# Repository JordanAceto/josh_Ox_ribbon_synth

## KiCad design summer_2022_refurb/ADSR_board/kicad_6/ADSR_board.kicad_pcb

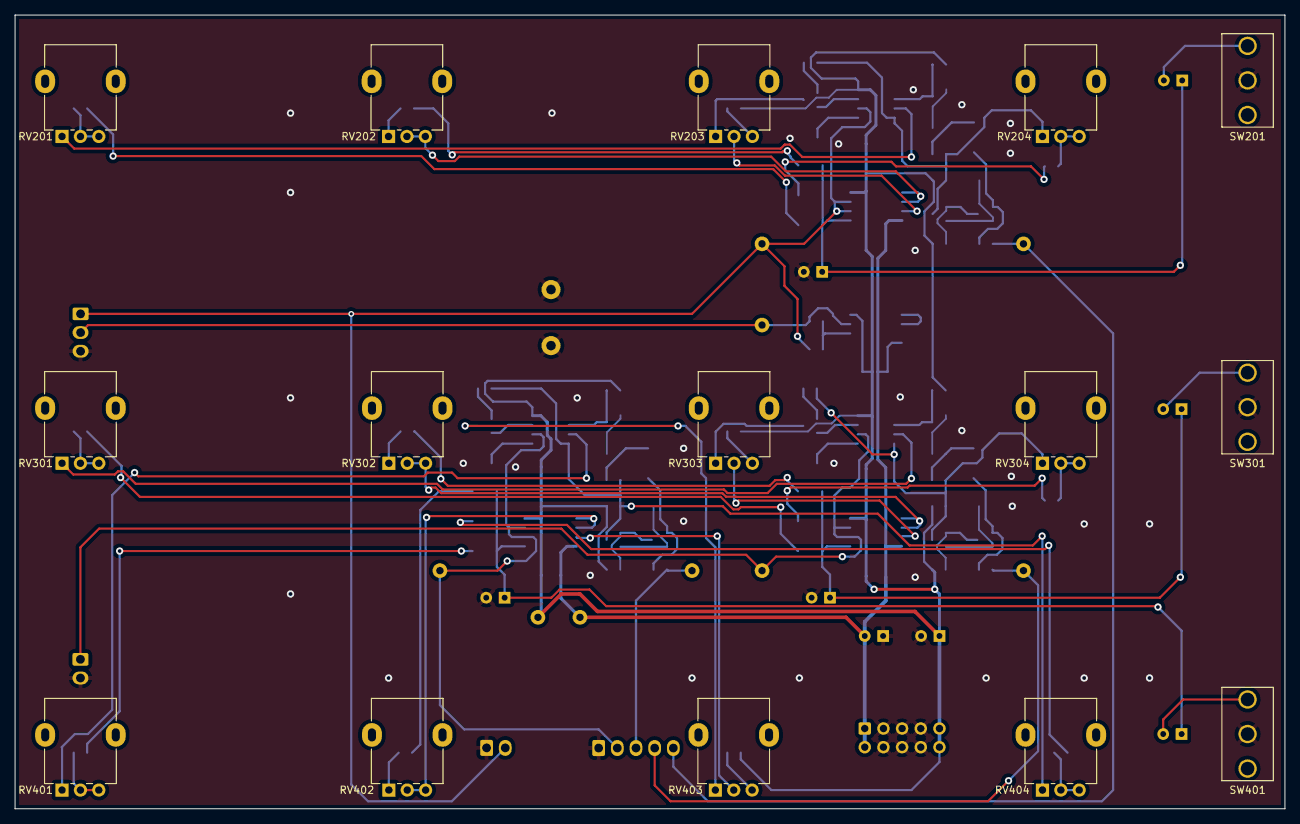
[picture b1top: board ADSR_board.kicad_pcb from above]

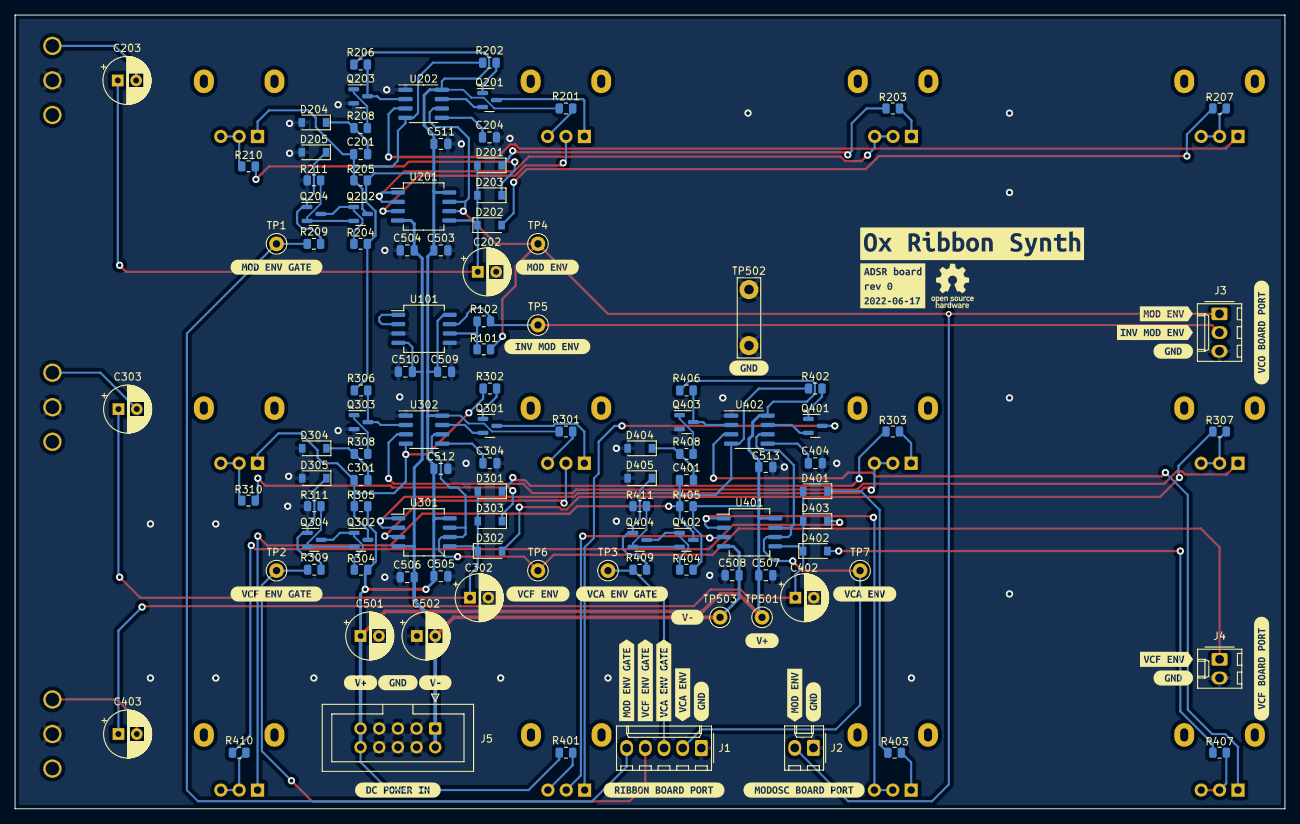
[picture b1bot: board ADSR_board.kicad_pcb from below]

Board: 2 copper layers, 172.7 x 107.9 mm, 156 parts (141 on the bottom side), 81 nets.

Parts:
C201, C204, C301, C304, C401, C404: 10n; C_0805_2012Metric
C202, C302, C402: 2u2; CP_Radial_D6.3mm_P2.50mm
C203, C303, C403: 22u; CP_Radial_D6.3mm_P2.50mm
C501, C502: 10u; CP_Radial_D6.3mm_P2.50mm
C503, C504, C505, C506, C507, C508, C509, C510, C511, C512, C513: 100n; C_0805_2012Metric
D201, D202, D203, D204, D205, D301, D302, D303, D304, D305, D401, D402, D403, D404, D405: 1N4148W; D_SOD-123
J1: ribbon_port; Molex_KK-254_AE-6410-05A_1x05_P2.54mm_Vertical
J2: modosc_port; Molex_KK-254_AE-6410-02A_1x02_P2.54mm_Vertical
J3: VCO_port; Molex_KK-254_AE-6410-03A_1x03_P2.54mm_Vertical
J4: VCF_port; Molex_KK-254_AE-6410-02A_1x02_P2.54mm_Vertical
J5: power_entry; IDC-Header_2x05_P2.54mm_Vertical
Q201, Q301, Q401: 2N7002; SOT-23
Q202, Q203, Q204, Q302, Q303, Q304, Q402, Q403, Q404: MMBT3904; SOT-23
R101, R102, R209, R309, R409: 100k; R_0805_2012Metric
R201, R301, R401: 4k7; R_0805_2012Metric
R202, R302, R402: 1M; R_0805_2012Metric
R203, R210, R211, R303, R310, R311, R403, R410, R411: 100; R_0805_2012Metric
R204, R205, R206, R208, R304, R305, R306, R308, R404, R405, R406, R408: 10k; R_0805_2012Metric
R207, R307, R407: 680; R_0805_2012Metric
RV201, RV202, RV204, RV301, RV302, RV304, RV401, RV402, RV404: 500kA; Potentiometer_Alpha_RD901F-40-00D_Single_Vertical
RV203, RV303, RV403: 10k; Potentiometer_Alpha_RD901F-40-00D_Single_Vertical
SW201, SW301, SW401: SW_SPDT; SPDT_mini_toggle
TP1: mod env gate; TestPoint_Keystone_5000-5004_Miniature
TP2: VCF env gate; TestPoint_Keystone_5000-5004_Miniature
TP3: VCA env gate; TestPoint_Keystone_5000-5004_Miniature
TP4: mod env; TestPoint_Keystone_5000-5004_Miniature
TP5: inv mod env; TestPoint_Keystone_5000-5004_Miniature
TP6: VCF env; TestPoint_Keystone_5000-5004_Miniature
TP7: VCA env; TestPoint_Keystone_5000-5004_Miniature
TP501: V+; TestPoint_Keystone_5000-5004_Miniature
TP502: GND; TestPoint_Bridge_Pitch7.62mm_Drill1.3mm
TP503: V-; TestPoint_Keystone_5000-5004_Miniature
U101, U201, U301, U401: TL072; SO-8_5.3x6.2mm_P1.27mm
U202, U302, U402: LM555xM; SOIC-8_3.9x4.9mm_P1.27mm
kibuzzard-62AC7A9F: G***; kibuzzard-62AC7A9F
kibuzzard-62AC7ABD: G***; kibuzzard-62AC7ABD
kibuzzard-62AC77C9: G***; kibuzzard-62AC77C9
kibuzzard-62AC77E4: G***; kibuzzard-62AC77E4
kibuzzard-62AC77FB: G***; kibuzzard-62AC77FB
kibuzzard-62AC78CB: G***; kibuzzard-62AC78CB
kibuzzard-62AC79A3: G***; kibuzzard-62AC79A3
kibuzzard-62AC79B4: G***; kibuzzard-62AC79B4
kibuzzard-62AC79C5: G***; kibuzzard-62AC79C5
kibuzzard-62AC79E0: G***; kibuzzard-62AC79E0
kibuzzard-62AC755C, kibuzzard-62AC755C#2, kibuzzard-62AC755C#3, kibuzzard-62AC755C#4, kibuzzard-62AC755C#5, kibuzzard-62AC755C#6: G***; kibuzzard-62AC755C
kibuzzard-62AC758B: G***; kibuzzard-62AC758B
kibuzzard-62AC762D: G***; kibuzzard-62AC762D
kibuzzard-62AC769B: G***; kibuzzard-62AC769B
kibuzzard-62AC791A, kibuzzard-62AC791A#2: G***; kibuzzard-62AC791A
kibuzzard-62AC792A, kibuzzard-62AC792A#2: G***; kibuzzard-62AC792A
kibuzzard-62AC795F: G***; kibuzzard-62AC795F
kibuzzard-62AC7596: G***; kibuzzard-62AC7596
kibuzzard-62AC7711: G***; kibuzzard-62AC7711
kibuzzard-62AC7737: G***; kibuzzard-62AC7737
kibuzzard-62AC7758: G***; kibuzzard-62AC7758
kibuzzard-62AC7771: G***; kibuzzard-62AC7771
kibuzzard-62AC7810: G***; kibuzzard-62AC7810
kibuzzard-62AC7972: G***; kibuzzard-62AC7972
kibuzzard-62AC7989: G***; kibuzzard-62AC7989

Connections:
+15V: C501.1, C503.1, C505.1, C507.1, C509.1, C511.1, C512.1, C513.1, J5.9, J5.10, R201.1, R204.1, R205.1, R206.1, R301.1, R304.1, R305.1, R306.1, R401.1, R404.1, R405.1, R406.1, TP501.1, U101.8 (V+), U201.8 (V+), U202.8 (VCC), U301.8 (V+), U302.8 (VCC), U401.8 (V+), U402.8 (VCC)
-15V: C502.2, C504.2, C506.2, C508.2, C510.2, J5.1, J5.2, TP503.1, U101.4 (V-), U201.4 (V-), U301.4 (V-), U401.4 (V-)
/VCA_ADSR/GATE: J1.3, R409.1, TP3.1
/VCA_ENV: J1.2, TP7.1, U401.6 (-), U401.7, U402.6 (THR)
/VCF_ADSR/GATE: J1.4, R309.1, TP2.1
/VCF_ADSR/OUT: J4.1, TP6.1, U301.6 (-), U301.7, U302.6 (THR)
/modulation_ADSR/GATE: J1.5, R209.1, TP1.1
/modulation_ADSR/OUT: J2.2, J3.1, R101.1, TP4.1, U201.6 (-), U201.7, U202.6 (THR)
GND: C202.2, C204.2, C302.2, C304.2, C402.2, C404.2, C501.2, C502.1, C503.2, C504.1, C505.2, C506.1, C507.2, C508.1, C509.2, C510.1, C511.2, C512.2, C513.2, D204.2 (A), D205.2 (A), D304.2 (A), D305.2 (A), D404.2 (A), D405.2 (A), J1.1, J2.1, J3.3, J4.2, J5.3, J5.4, J5.5, J5.6, J5.7, J5.8, Q203.2 (E), Q303.2 (E), Q403.2 (E), R211.2, R311.2, R411.2, SW201.2 (B), SW301.2 (B), SW401.2 (B), TP502.1, U101.3 (+), U101.5 (+), U202.1 (GND), U302.1 (GND), U402.1 (GND)
unnamed: C201.1, Q202.3 (C), R202.1, R205.2, RV204.1, U202.4 (R)
unnamed: C201.2, D204.1 (K), R208.1
unnamed: C202.1, C203.1, D201.2 (A), D202.1 (K), D203.2 (A), U201.5 (+)
unnamed: C203.2, SW201.3 (C)
unnamed: C204.1, U202.5 (CV)
unnamed: C301.1, Q302.3 (C), R302.1, R305.2, RV304.1, U302.4 (R)
unnamed: C301.2, D304.1 (K), R308.1
unnamed: C302.1, C303.1, D301.2 (A), D302.1 (K), D303.2 (A), U301.5 (+)
unnamed: C303.2, SW301.3 (C)
unnamed: C304.1, U302.5 (CV)
unnamed: C401.1, Q402.3 (C), R402.1, R405.2, RV404.1, U402.4 (R)
unnamed: C401.2, D404.1 (K), R408.1
unnamed: C402.1, C403.1, D401.2 (A), D402.1 (K), D403.2 (A), U401.5 (+)
unnamed: C403.2, SW401.3 (C)
unnamed: C404.1, U402.5 (CV)
unnamed: D201.1 (K), R203.2
unnamed: D202.2 (A), R207.2
unnamed: D203.1 (K), R210.1
unnamed: D205.1 (K), Q204.1 (B), R209.2
unnamed: D301.1 (K), R303.2
unnamed: D302.2 (A), R307.2
unnamed: D303.1 (K), R310.1
unnamed: D305.1 (K), Q304.1 (B), R309.2
unnamed: D401.1 (K), R403.2
unnamed: D402.2 (A), R407.2
unnamed: D403.1 (K), R410.1
unnamed: D405.1 (K), Q404.1 (B), R409.2
unnamed: J3.2, R102.2, TP5.1, U101.7
unnamed: Q201.1 (G), R202.2
unnamed: Q201.2 (S), U202.7 (DIS)
unnamed: Q201.3 (D), RV203.1
unnamed: Q202.1 (B), Q204.3 (C), R204.2
unnamed: Q202.2 (E), Q204.2 (E), R211.1
unnamed: Q203.1 (B), R208.2
unnamed: Q203.3 (C), R206.2, U202.2 (TR)
unnamed: Q301.1 (G), R302.2
unnamed: Q301.2 (S), U302.7 (DIS)
unnamed: Q301.3 (D), RV303.1
unnamed: Q302.1 (B), Q304.3 (C), R304.2
unnamed: Q302.2 (E), Q304.2 (E), R311.1
unnamed: Q303.1 (B), R308.2
unnamed: Q303.3 (C), R306.2, U302.2 (TR)
unnamed: Q401.1 (G), R402.2
unnamed: Q401.2 (S), U402.7 (DIS)
unnamed: Q401.3 (D), RV403.1
unnamed: Q402.1 (B), Q404.3 (C), R404.2
unnamed: Q402.2 (E), Q404.2 (E), R411.1
unnamed: Q403.1 (B), R408.2
unnamed: Q403.3 (C), R406.2, U402.2 (TR)
unnamed: R101.2, R102.1, U101.6 (-)
unnamed: R201.2, RV203.3
unnamed: R203.1, RV202.1
unnamed: R207.1, RV201.2, RV201.3
unnamed: R210.2, RV204.2, RV204.3
unnamed: R301.2, RV303.3
unnamed: R303.1, RV302.1
unnamed: R307.1, RV301.2, RV301.3
unnamed: R310.2, RV304.2, RV304.3
unnamed: R401.2, RV403.3
unnamed: R403.1, RV402.1
unnamed: R407.1, RV401.2, RV401.3
unnamed: R410.2, RV404.2, RV404.3
unnamed: RV201.1, U202.3 (Q)
unnamed: RV202.2, RV202.3, U201.1, U201.2 (-)
unnamed: RV203.2, U201.3 (+)
unnamed: RV301.1, U302.3 (Q)
unnamed: RV302.2, RV302.3, U301.1, U301.2 (-)
unnamed: RV303.2, U301.3 (+)
unnamed: RV401.1, U402.3 (Q)
unnamed: RV402.2, RV402.3, U401.1, U401.2 (-)
unnamed: RV403.2, U401.3 (+)
unnamed: U101.1, U101.2 (-)

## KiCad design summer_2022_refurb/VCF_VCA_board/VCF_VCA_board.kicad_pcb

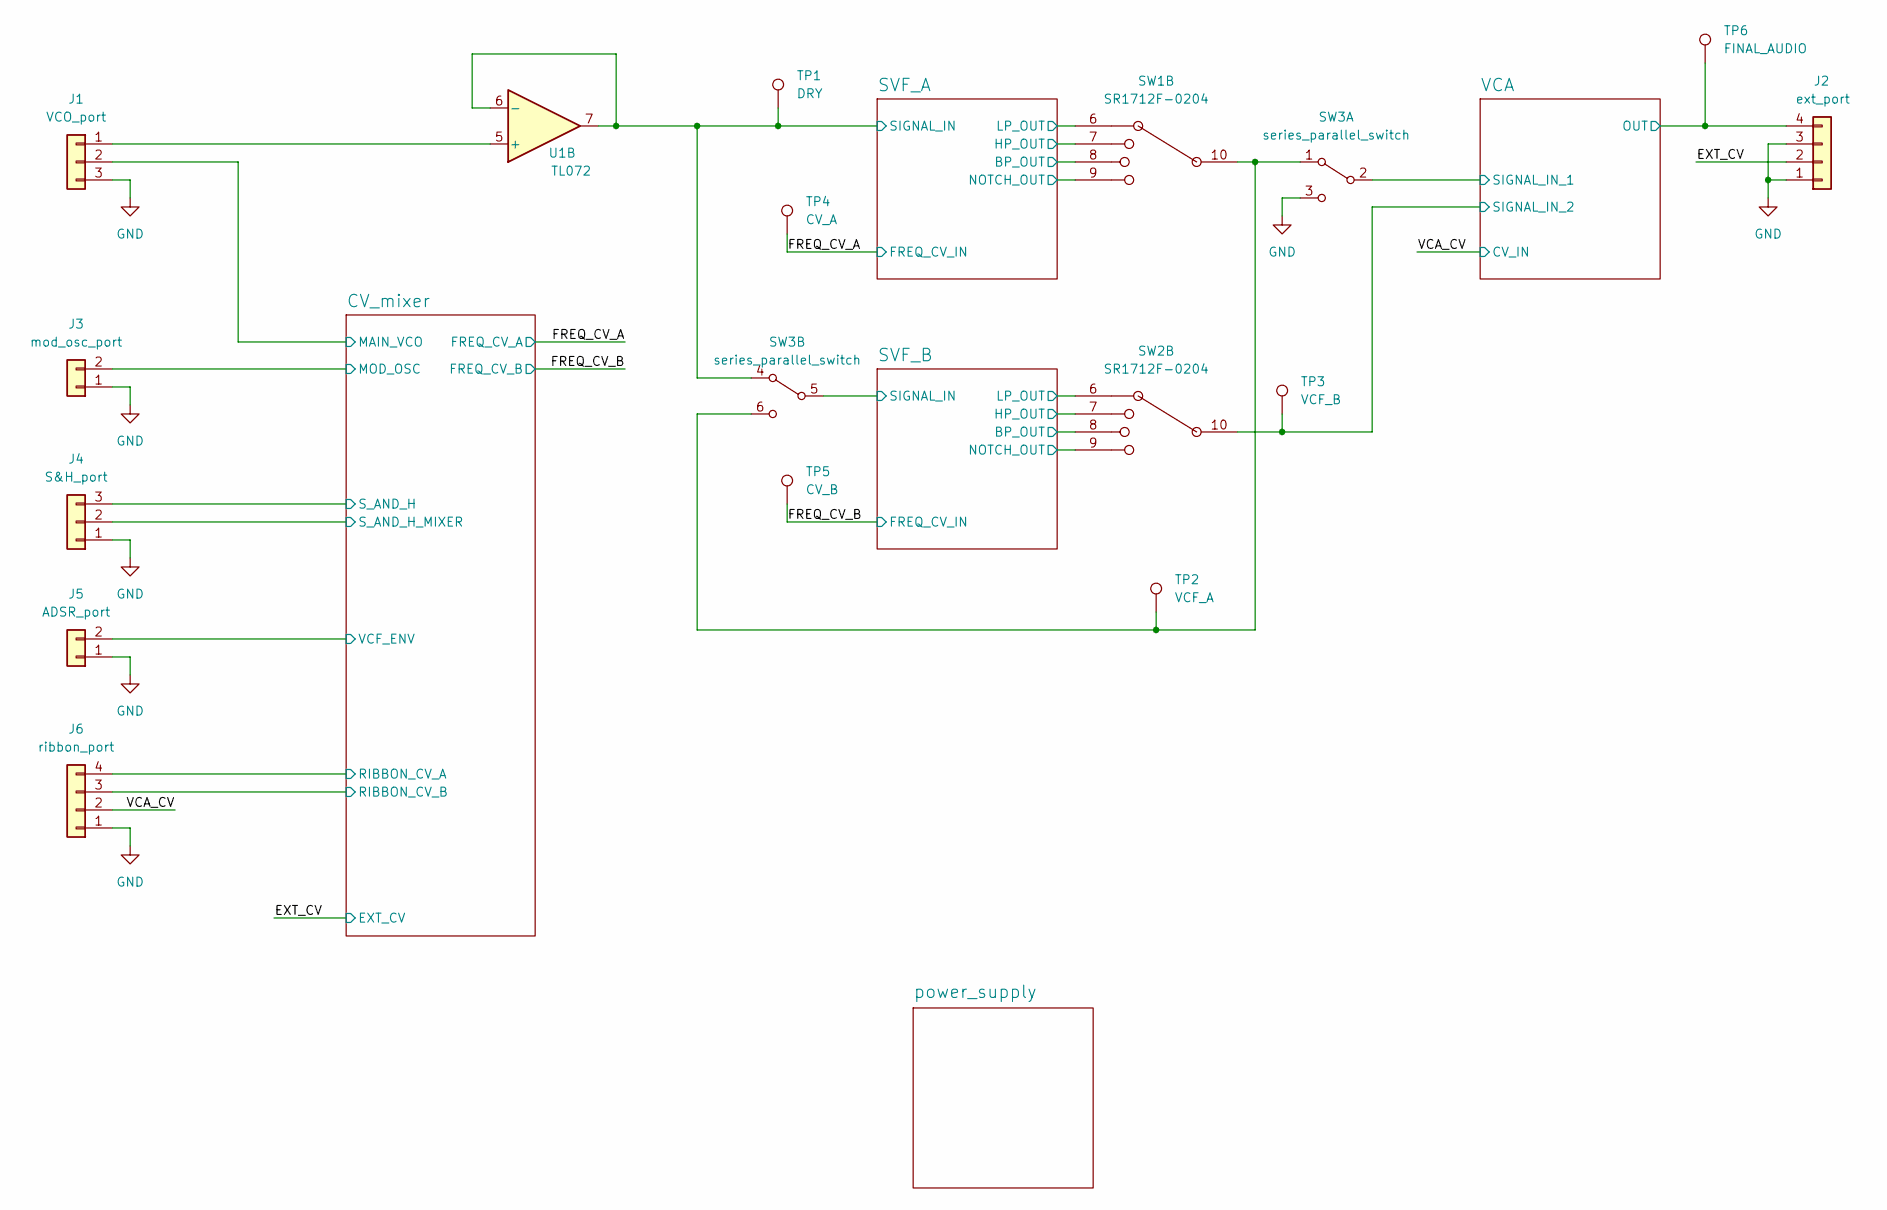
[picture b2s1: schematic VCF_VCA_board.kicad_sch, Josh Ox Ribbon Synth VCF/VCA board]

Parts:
J1: VCO_port; Molex_KK-254_AE-6410-03A_1x03_P2.54mm_Vertical
J2: ext_port; Molex_KK-254_AE-6410-04A_1x04_P2.54mm_Vertical
J3: mod_osc_port; Molex_KK-254_AE-6410-02A_1x02_P2.54mm_Vertical
J4: S&H_port; Molex_KK-254_AE-6410-03A_1x03_P2.54mm_Vertical
J5: ADSR_port; Molex_KK-254_AE-6410-02A_1x02_P2.54mm_Vertical
J6: ribbon_port; Molex_KK-254_AE-6410-04A_1x04_P2.54mm_Vertical
SW1, SW2: SR1712F-0204; SR1712F_rotary_switch
SW3: series_parallel_switch; DPDT_mini_toggle
TP1: DRY; TestPoint_Keystone_5000-5004_Miniature
TP2: VCF_A; TestPoint_Keystone_5000-5004_Miniature
TP3: VCF_B; TestPoint_Keystone_5000-5004_Miniature
TP4: CV_A; TestPoint_Keystone_5000-5004_Miniature
TP5: CV_B; TestPoint_Keystone_5000-5004_Miniature
TP6: FINAL_AUDIO; TestPoint_Keystone_5000-5004_Miniature
U1: TL072; SO-8_5.3x6.2mm_P1.27mm

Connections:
/CV_mixer/MAIN_VCO: J1.2; also elsewhere on the board
/CV_mixer/MOD_OSC: J3.2; also elsewhere on the board
/CV_mixer/RIBBON_CV_A: J6.4; also elsewhere on the board
/CV_mixer/RIBBON_CV_B: J6.3; also elsewhere on the board
/CV_mixer/S_AND_H: J4.3; also elsewhere on the board
/CV_mixer/S_AND_H_MIXER: J4.2; also elsewhere on the board
/CV_mixer/VCF_ENV: J5.2; also elsewhere on the board
/EXT_CV: J2.2; also elsewhere on the board
/FREQ_CV_A: TP4.1; also elsewhere on the board
/FREQ_CV_B: TP5.1; also elsewhere on the board
/SVF_A/BP_OUT: SW1.8; also elsewhere on the board
/SVF_A/HP_OUT: SW1.7; also elsewhere on the board
/SVF_A/LP_OUT: SW1.6; also elsewhere on the board
/SVF_A/NOTCH_OUT: SW1.9; also elsewhere on the board
/SVF_A/SIGNAL_IN: SW3.4 (A), TP1.1, U1.6 (-), U1.7; also elsewhere on the board
/SVF_B/BP_OUT: SW2.8; also elsewhere on the board
/SVF_B/HP_OUT: SW2.7; also elsewhere on the board
/SVF_B/LP_OUT: SW2.6; also elsewhere on the board
/SVF_B/NOTCH_OUT: SW2.9; also elsewhere on the board
/SVF_B/SIGNAL_IN: SW3.5 (B); also elsewhere on the board
/VCA/OUT: J2.4, TP6.1; also elsewhere on the board
/VCA/SIGNAL_IN_1: SW3.2 (B); also elsewhere on the board
/VCA/SIGNAL_IN_2: SW2.10, TP3.1; also elsewhere on the board
/VCA_CV: J6.2; also elsewhere on the board
unnamed: J1.1, U1.5 (+)
unnamed: SW1.10, SW3.1 (A), SW3.6 (C), TP2.1

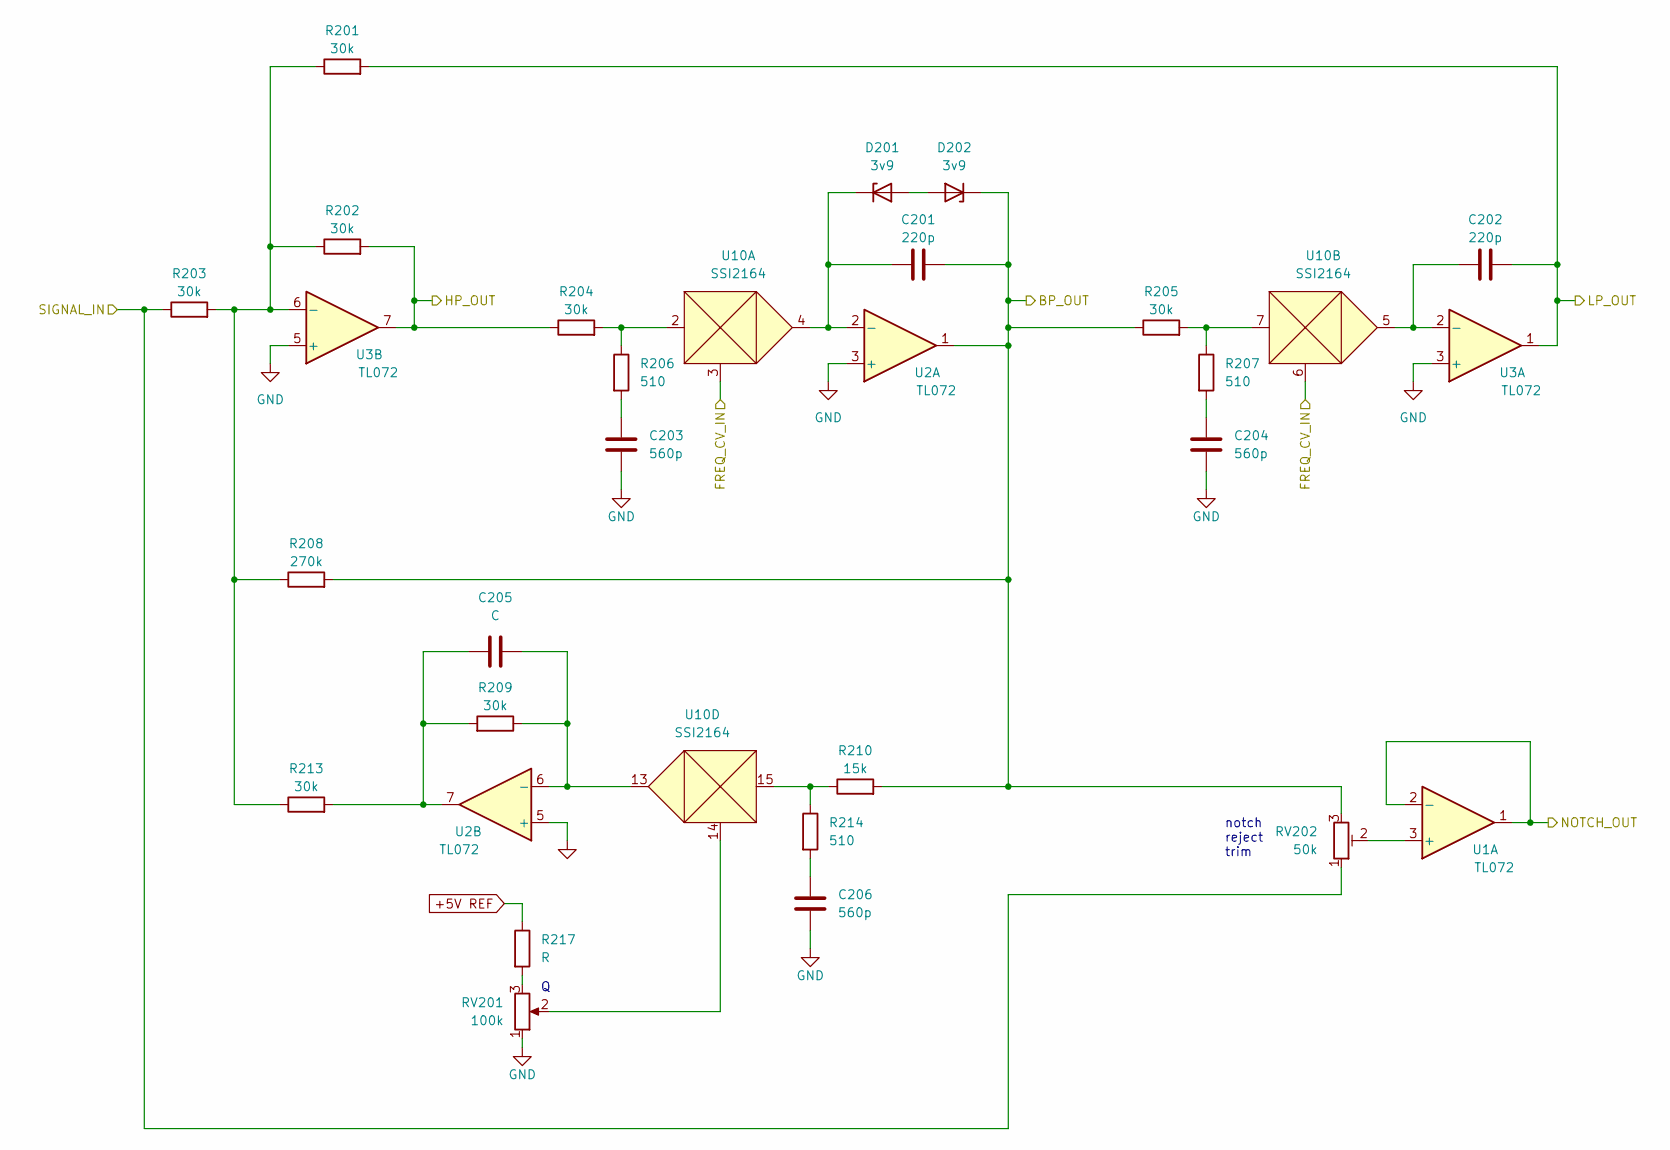
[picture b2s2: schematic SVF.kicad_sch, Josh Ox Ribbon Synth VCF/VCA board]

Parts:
C201, C202: 220p; C_Rect_L7.2mm_W4.5mm_P5.00mm_FKS2_FKP2_MKS2_MKP2
C203, C204, C206: 560p; C_0805_2012Metric
C205: C; C_0805_2012Metric
D201, D202: 3v9; D_SOD-123
R201, R202, R203, R204, R205, R209, R213: 30k; R_0805_2012Metric
R206, R207, R214: 510; R_0805_2012Metric
R208: 270k; R_0805_2012Metric
R210: 15k; R_0805_2012Metric
R217: R; R_0805_2012Metric
RV201: 100k; Potentiometer_Alpha_RD901F-40-00D_Single_Vertical
RV202: 50k; Potentiometer_Bourns_3296W_Vertical
U1, U2, U3: TL072; SO-8_5.3x6.2mm_P1.27mm
U10: SSI2164; SOIC-16_3.9x9.9mm_P1.27mm

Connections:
+5V REF: R217.1; also elsewhere on the board
/FREQ_CV_A: U10.3, U10.6; also elsewhere on the board
/SVF_A/BP_OUT: C201.2, D202.1 (K), R205.1, R208.2, R210.2, RV202.3, U2.1; also elsewhere on the board
/SVF_A/HP_OUT: R202.2, R204.1, U3.7; also elsewhere on the board
/SVF_A/LP_OUT: C202.2, R201.2, U3.1; also elsewhere on the board
/SVF_A/NOTCH_OUT: U1.1, U1.2 (-); also elsewhere on the board
/SVF_A/SIGNAL_IN: R203.1, RV202.1; also elsewhere on the board
unnamed: C201.1, D201.1 (K), U2.2 (-), U10.4
unnamed: C202.1, U3.2 (-), U10.5
unnamed: C203.1, R206.2
unnamed: C204.1, R207.2
unnamed: C205.1, R209.2, R213.2, U2.7
unnamed: C205.2, R209.1, U2.6 (-), U10.13
unnamed: C206.1, R214.2
unnamed: D201.2 (A), D202.2 (A)
unnamed: R201.1, R202.1, R203.2, R208.1, R213.1, U3.6 (-)
unnamed: R204.2, R206.1, U10.2
unnamed: R205.2, R207.1, U10.7
unnamed: R210.1, R214.1, U10.15
unnamed: R217.2, RV201.3
unnamed: RV201.2, U10.14
unnamed: RV202.2, U1.3 (+)

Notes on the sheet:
notch reject trim

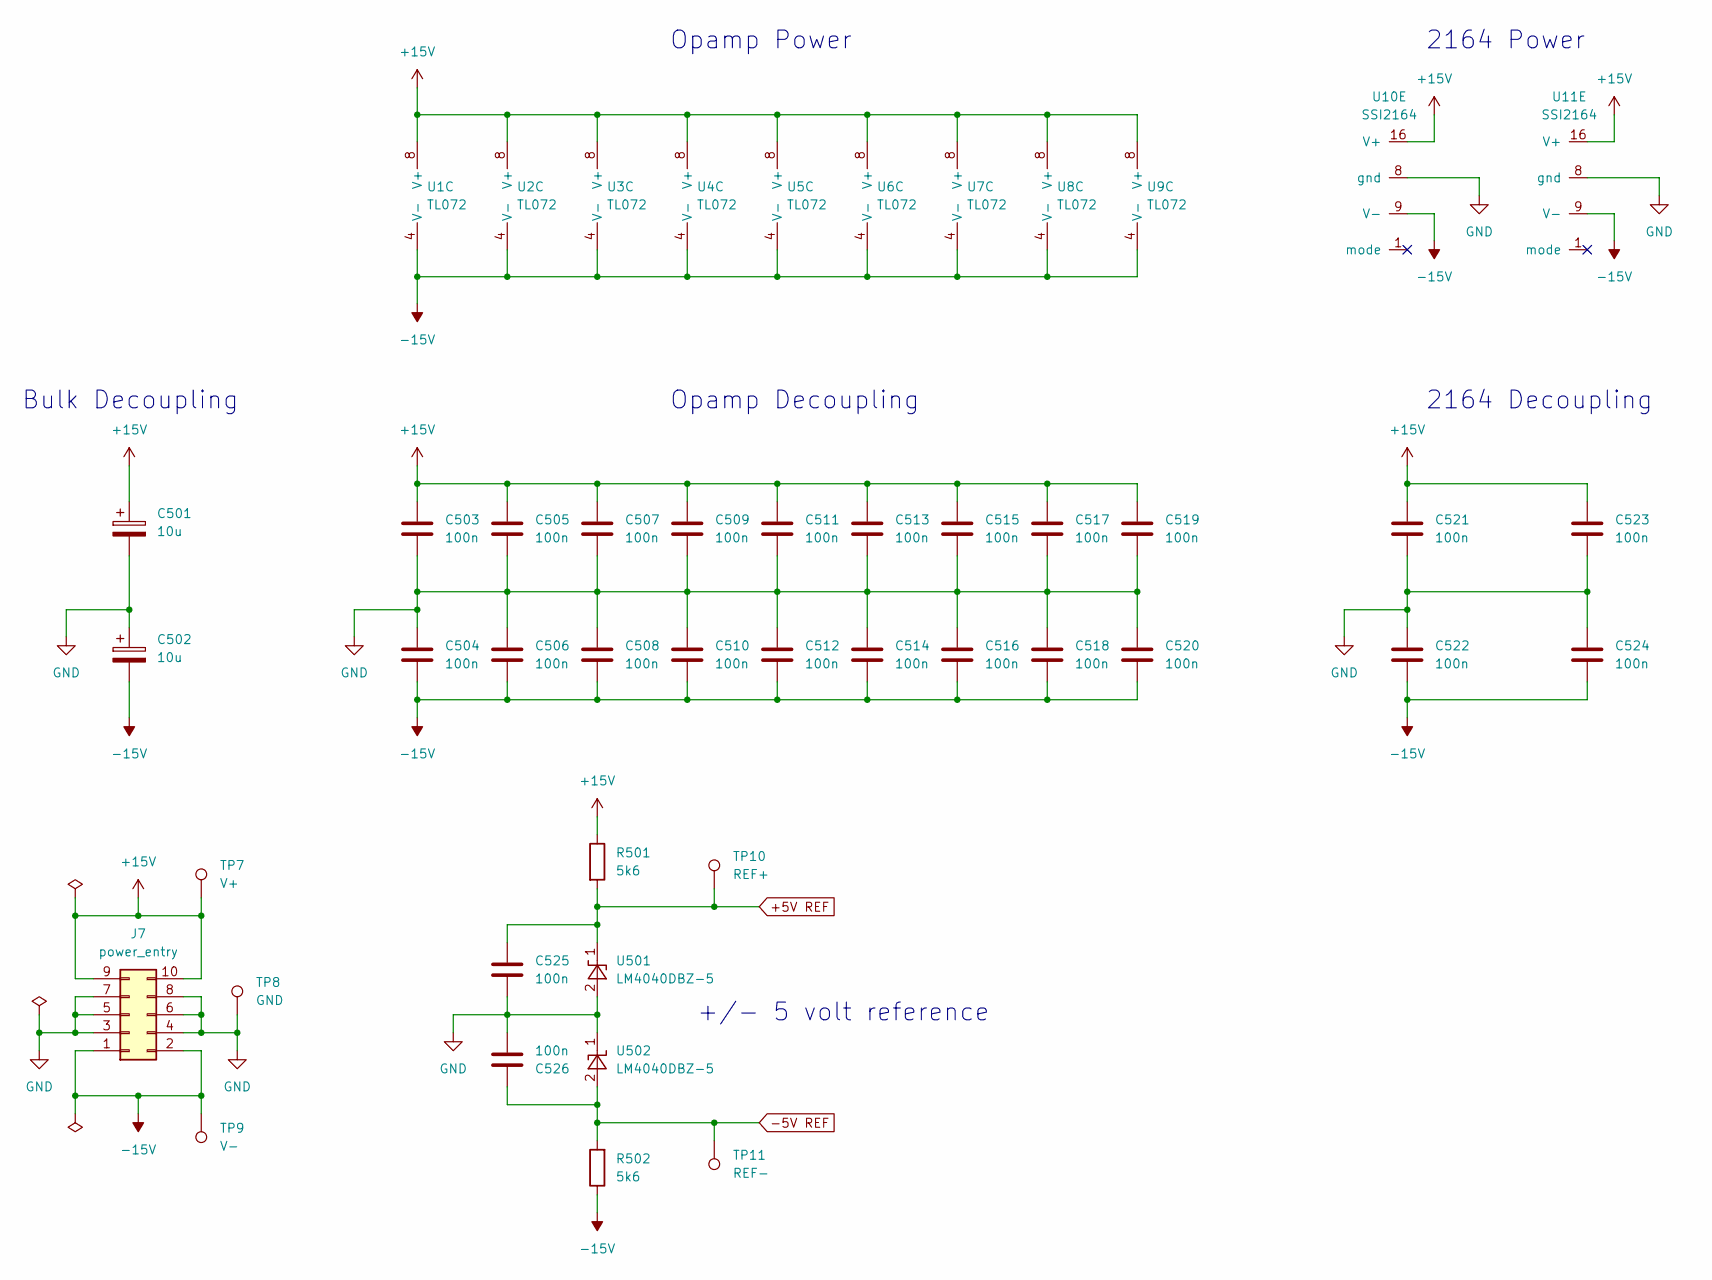
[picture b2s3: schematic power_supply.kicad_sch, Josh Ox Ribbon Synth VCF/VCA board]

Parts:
C501, C502: 10u; CP_Radial_D6.3mm_P2.50mm
C503, C504, C505, C506, C507, C508, C509, C510, C511, C512, C513, C514, C515, C516, C517, C518, C519, C520, C521, C522, C523, C524, C525, C526: 100n; C_0805_2012Metric
J7: power_entry; IDC-Header_2x05_P2.54mm_Vertical
R501, R502: 5k6; R_0805_2012Metric
TP7: V+; TestPoint_Keystone_5000-5004_Miniature
TP8: GND; TestPoint_Bridge_Pitch7.62mm_Drill1.3mm
TP9: V-; TestPoint_Keystone_5000-5004_Miniature
TP10: REF+; TestPoint_Keystone_5000-5004_Miniature
TP11: REF-; TestPoint_Keystone_5000-5004_Miniature
U1, U2, U3, U4, U5, U6, U7, U8, U9: TL072; SO-8_5.3x6.2mm_P1.27mm
U10, U11: SSI2164; SOIC-16_3.9x9.9mm_P1.27mm
U501, U502: LM4040DBZ-5; SOT-23

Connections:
+5V REF: C525.1, R501.2, TP10.1, U501.1 (K); also elsewhere on the board
+15V: C501.1, C503.1, C505.1, C507.1, C509.1, C511.1, C513.1, C515.1, C517.1, C519.1, C521.1, C523.1, J7.9, J7.10, R501.1, TP7.1, U1.8 (V+), U2.8 (V+), U3.8 (V+), U4.8 (V+), U5.8 (V+), U6.8 (V+), U7.8 (V+), U8.8 (V+), U9.8 (V+), U10.16 (V+), U11.16 (V+)
-5V REF: C526.1, R502.2, TP11.1, U502.2 (A); also elsewhere on the board
-15V: C502.2, C504.2, C506.2, C508.2, C510.2, C512.2, C514.2, C516.2, C518.2, C520.2, C522.2, C524.2, J7.1, J7.2, R502.1, TP9.1, U1.4 (V-), U2.4 (V-), U3.4 (V-), U4.4 (V-), U5.4 (V-), U6.4 (V-), U7.4 (V-), U8.4 (V-), U9.4 (V-), U10.9 (V-), U11.9 (V-)
/FREQ_CV_B: U11.3, U11.6; also elsewhere on the board
/SVF_B/BP_OUT: U4.1; also elsewhere on the board
/SVF_B/HP_OUT: U5.7; also elsewhere on the board
/SVF_B/LP_OUT: U5.1; also elsewhere on the board
/SVF_B/NOTCH_OUT: U6.6 (-), U6.7; also elsewhere on the board
unnamed 35: U4.2 (-), U11.4; also elsewhere on the board
unnamed 36: U5.2 (-), U11.5; also elsewhere on the board
unnamed 39: U4.7; also elsewhere on the board
unnamed 40: U4.6 (-), U11.13; also elsewhere on the board
unnamed 68: U5.6 (-); also elsewhere on the board
unnamed 69: U11.2; also elsewhere on the board
unnamed 70: U11.7; also elsewhere on the board
unnamed 71: U11.15; also elsewhere on the board
unnamed 90: U11.14; also elsewhere on the board
unnamed 91: U6.5 (+); also elsewhere on the board

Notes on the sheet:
Opamp Power
2164 Decoupling
+/- 5 volt reference
2164 Power
Bulk Decoupling
Opamp Decoupling

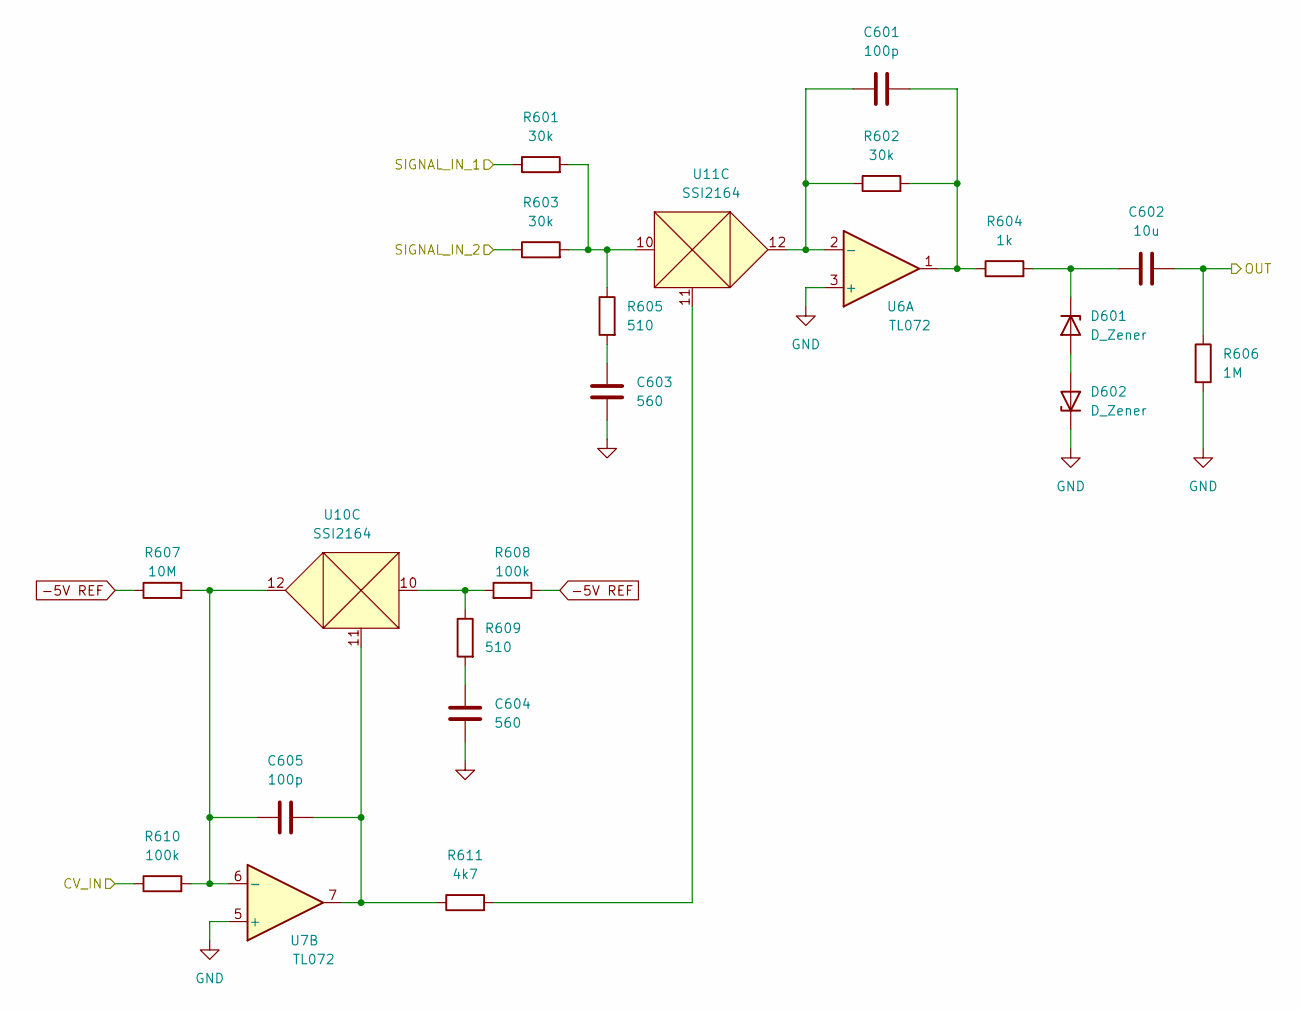
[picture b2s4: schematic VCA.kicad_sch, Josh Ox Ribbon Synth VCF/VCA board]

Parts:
C601, C605: 100p; C_0805_2012Metric
C602: 10u; C_Radial_D6.3mm_H5.0mm_P2.50mm
C603, C604: 560; C_0805_2012Metric
D601, D602: D_Zener; D_SOD-123
R601, R602, R603: 30k; R_0805_2012Metric
R604: 1k; R_0805_2012Metric
R605, R609: 510; R_0805_2012Metric
R606: 1M; R_0805_2012Metric
R607: 10M; R_0805_2012Metric
R608, R610: 100k; R_0805_2012Metric
R611: 4k7; R_0805_2012Metric
U6, U7: TL072; SO-8_5.3x6.2mm_P1.27mm
U10, U11: SSI2164; SOIC-16_3.9x9.9mm_P1.27mm

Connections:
-5V REF: R607.1, R608.1; also elsewhere on the board
/FREQ_CV_B: U11.3, U11.6; also elsewhere on the board
/SVF_B/NOTCH_OUT: U6.6 (-), U6.7; also elsewhere on the board
/VCA/OUT: C602.2, R606.1; also elsewhere on the board
/VCA/SIGNAL_IN_1: R601.1; also elsewhere on the board
/VCA/SIGNAL_IN_2: R603.1; also elsewhere on the board
/VCA_CV: R610.1; also elsewhere on the board
unnamed 35: U11.4; also elsewhere on the board
unnamed 36: U11.5; also elsewhere on the board
unnamed 40: U11.13; also elsewhere on the board
unnamed: C601.1, R602.1, U6.2 (-), U11.12
unnamed: C601.2, R602.2, R604.1, U6.1
unnamed: C602.1, D601.1 (K), R604.2
unnamed: C603.1, R605.2
unnamed: C604.1, R609.2
unnamed: C605.1, R607.2, R610.2, U7.6 (-), U10.12
unnamed: C605.2, R611.1, U7.7, U10.11
unnamed: D601.2 (A), D602.2 (A)
unnamed 69: U11.2; also elsewhere on the board
unnamed 70: U11.7; also elsewhere on the board
unnamed 71: U11.15; also elsewhere on the board
unnamed: R601.2, R603.2, R605.1, U11.10
unnamed: R608.2, R609.1, U10.10
unnamed: R611.2, U11.11
unnamed 90: U11.14; also elsewhere on the board
unnamed 91: U6.5 (+); also elsewhere on the board

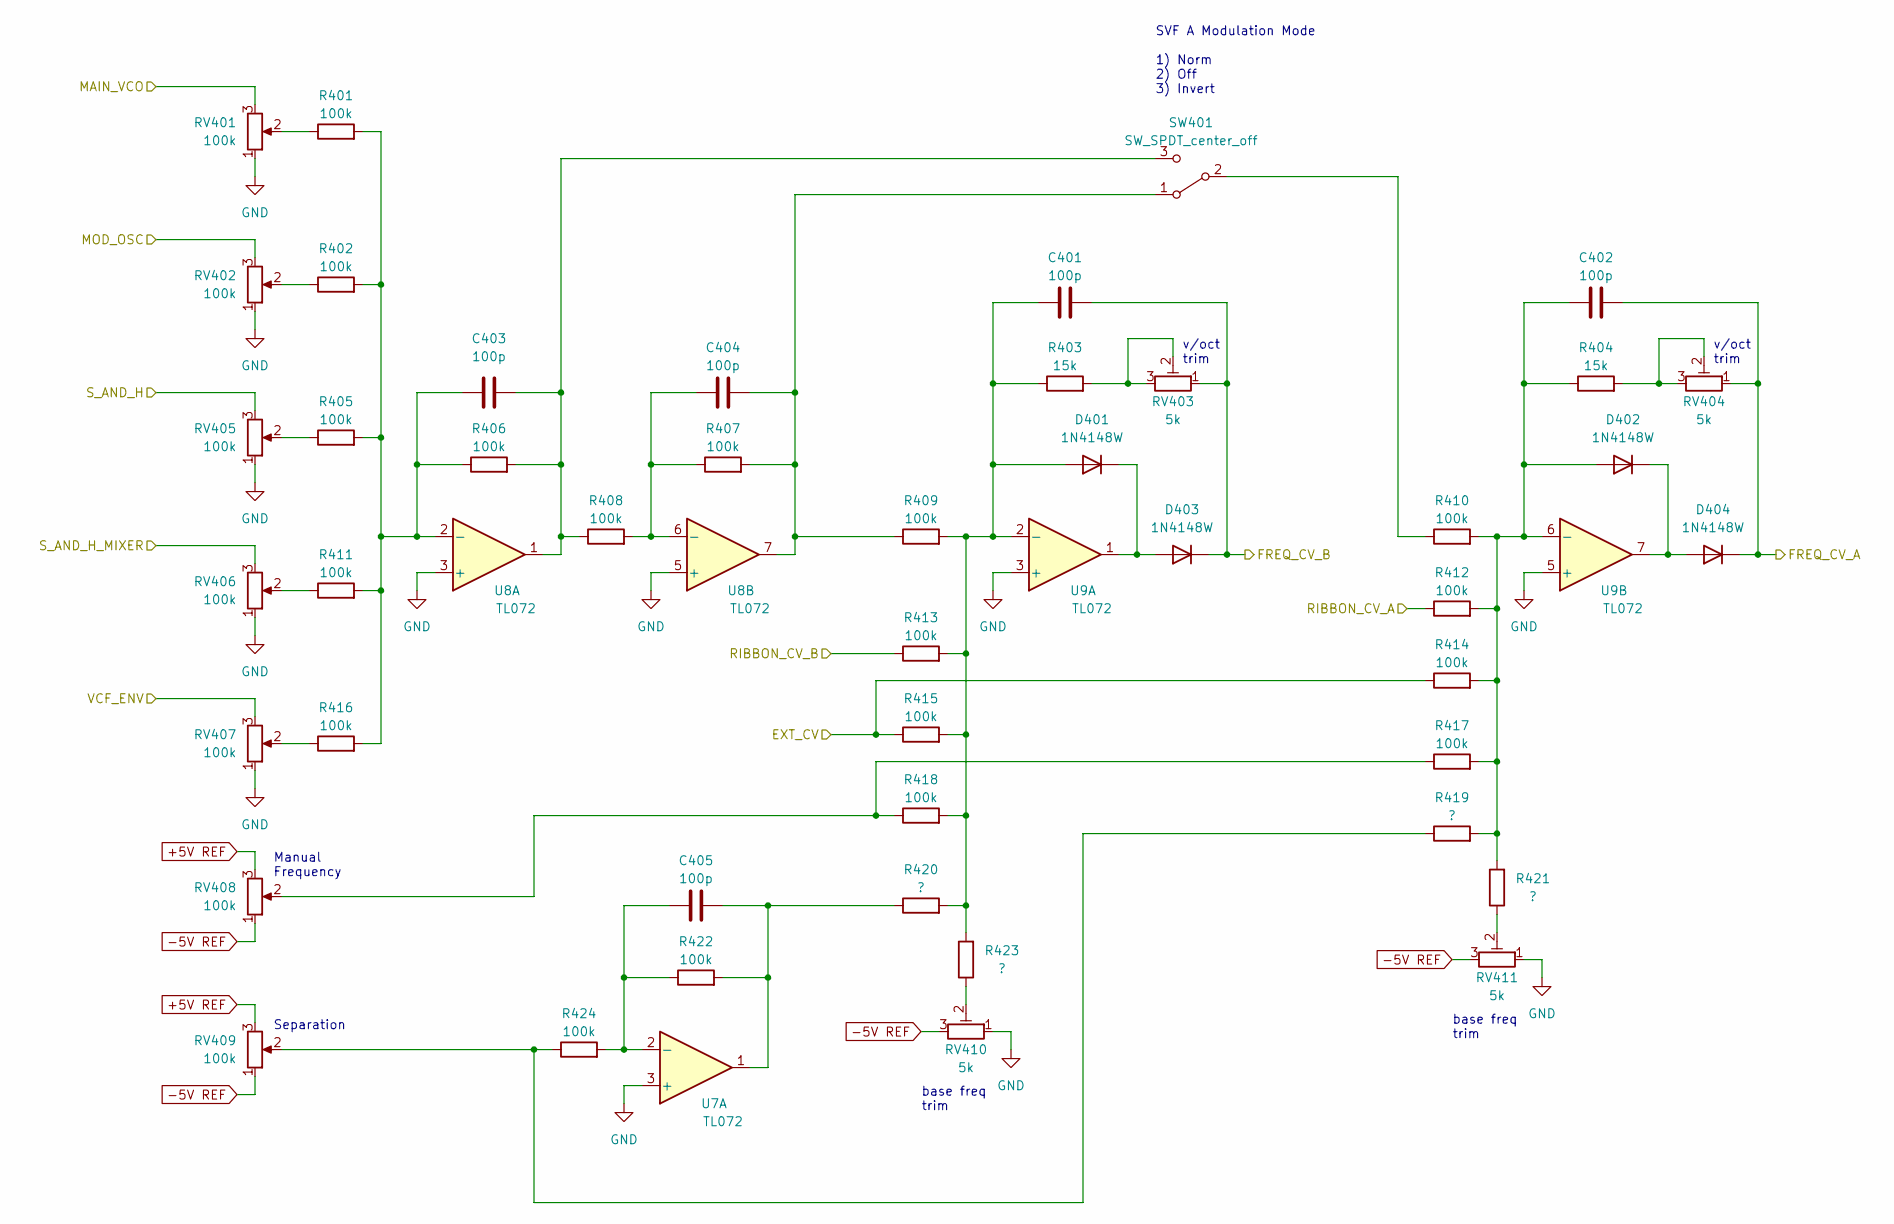
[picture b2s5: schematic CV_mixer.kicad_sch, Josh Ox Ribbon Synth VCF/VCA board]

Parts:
C401, C402, C403, C404, C405: 100p; C_0805_2012Metric
D401, D402, D403, D404: 1N4148W; D_SOD-123
R401, R402, R405, R406, R407, R408, R409, R410, R411, R412, R413, R414, R415, R416, R417, R418, R422, R424: 100k; R_0805_2012Metric
R403, R404: 15k; R_0805_2012Metric
R419, R420, R421, R423: ?; R_0805_2012Metric
RV401, RV402, RV405, RV406, RV407, RV408, RV409: 100k; Potentiometer_Alpha_RD901F-40-00D_Single_Vertical
RV403, RV404, RV410, RV411: 5k; Potentiometer_Bourns_3296W_Vertical
SW401: SW_SPDT_center_off; SPDT_mini_toggle
U7, U8, U9: TL072; SO-8_5.3x6.2mm_P1.27mm

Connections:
+5V REF: RV408.3, RV409.3; also elsewhere on the board
-5V REF: RV408.1, RV409.1, RV410.3, RV411.3; also elsewhere on the board
/CV_mixer/MAIN_VCO: RV401.3; also elsewhere on the board
/CV_mixer/MOD_OSC: RV402.3; also elsewhere on the board
/CV_mixer/RIBBON_CV_A: R412.1; also elsewhere on the board
/CV_mixer/RIBBON_CV_B: R413.1; also elsewhere on the board
/CV_mixer/S_AND_H: RV405.3; also elsewhere on the board
/CV_mixer/S_AND_H_MIXER: RV406.3; also elsewhere on the board
/CV_mixer/VCF_ENV: RV407.3; also elsewhere on the board
/EXT_CV: R414.1, R415.1; also elsewhere on the board
/FREQ_CV_A: C402.2, D404.1 (K), RV404.1; also elsewhere on the board
/FREQ_CV_B: C401.2, D403.1 (K), RV403.1; also elsewhere on the board
unnamed: C401.1, D401.2 (A), R403.1, R409.2, R413.2, R415.2, R418.2, R420.2, R423.2, U9.2 (-)
unnamed: C402.1, D402.2 (A), R404.1, R410.2, R412.2, R414.2, R417.2, R419.2, R421.2, U9.6 (-)
unnamed: C403.1, R401.2, R402.2, R405.2, R406.1, R411.2, R416.2, U8.2 (-)
unnamed: C403.2, R406.2, R408.1, SW401.3 (C), U8.1
unnamed: C404.1, R407.1, R408.2, U8.6 (-)
unnamed: C404.2, R407.2, R409.1, SW401.1 (A), U8.7
unnamed: C405.1, R422.1, R424.2, U7.2 (-)
unnamed: C405.2, R420.1, R422.2, U7.1
unnamed: D401.1 (K), D403.2 (A), U9.1
unnamed: D402.1 (K), D404.2 (A), U9.7
unnamed: R401.1, RV401.2
unnamed: R402.1, RV402.2
unnamed: R403.2, RV403.2, RV403.3
unnamed: R404.2, RV404.2, RV404.3
unnamed: R405.1, RV405.2
unnamed: R410.1, SW401.2 (B)
unnamed: R411.1, RV406.2
unnamed: R416.1, RV407.2
unnamed: R417.1, R418.1, RV408.2
unnamed: R419.1, R424.1, RV409.2
unnamed: R421.1, RV411.2
unnamed: R423.1, RV410.2

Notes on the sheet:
Manual Frequency
SVF A Modulation Mode 1) Norm 2) Off 3) Invert
Separation
base freq trim
v/oct trim

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

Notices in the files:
summer_2022_refurb/ADSR_board/kicad_6/ADSR_board.kicad_pcb:
creativecommons.org/licences/by/4.0
license: CC by 4.0
summer_2022_refurb/VCF_VCA_board/CV_mixer.kicad_sch:
creativecommons.org/licenses/by/4.0
